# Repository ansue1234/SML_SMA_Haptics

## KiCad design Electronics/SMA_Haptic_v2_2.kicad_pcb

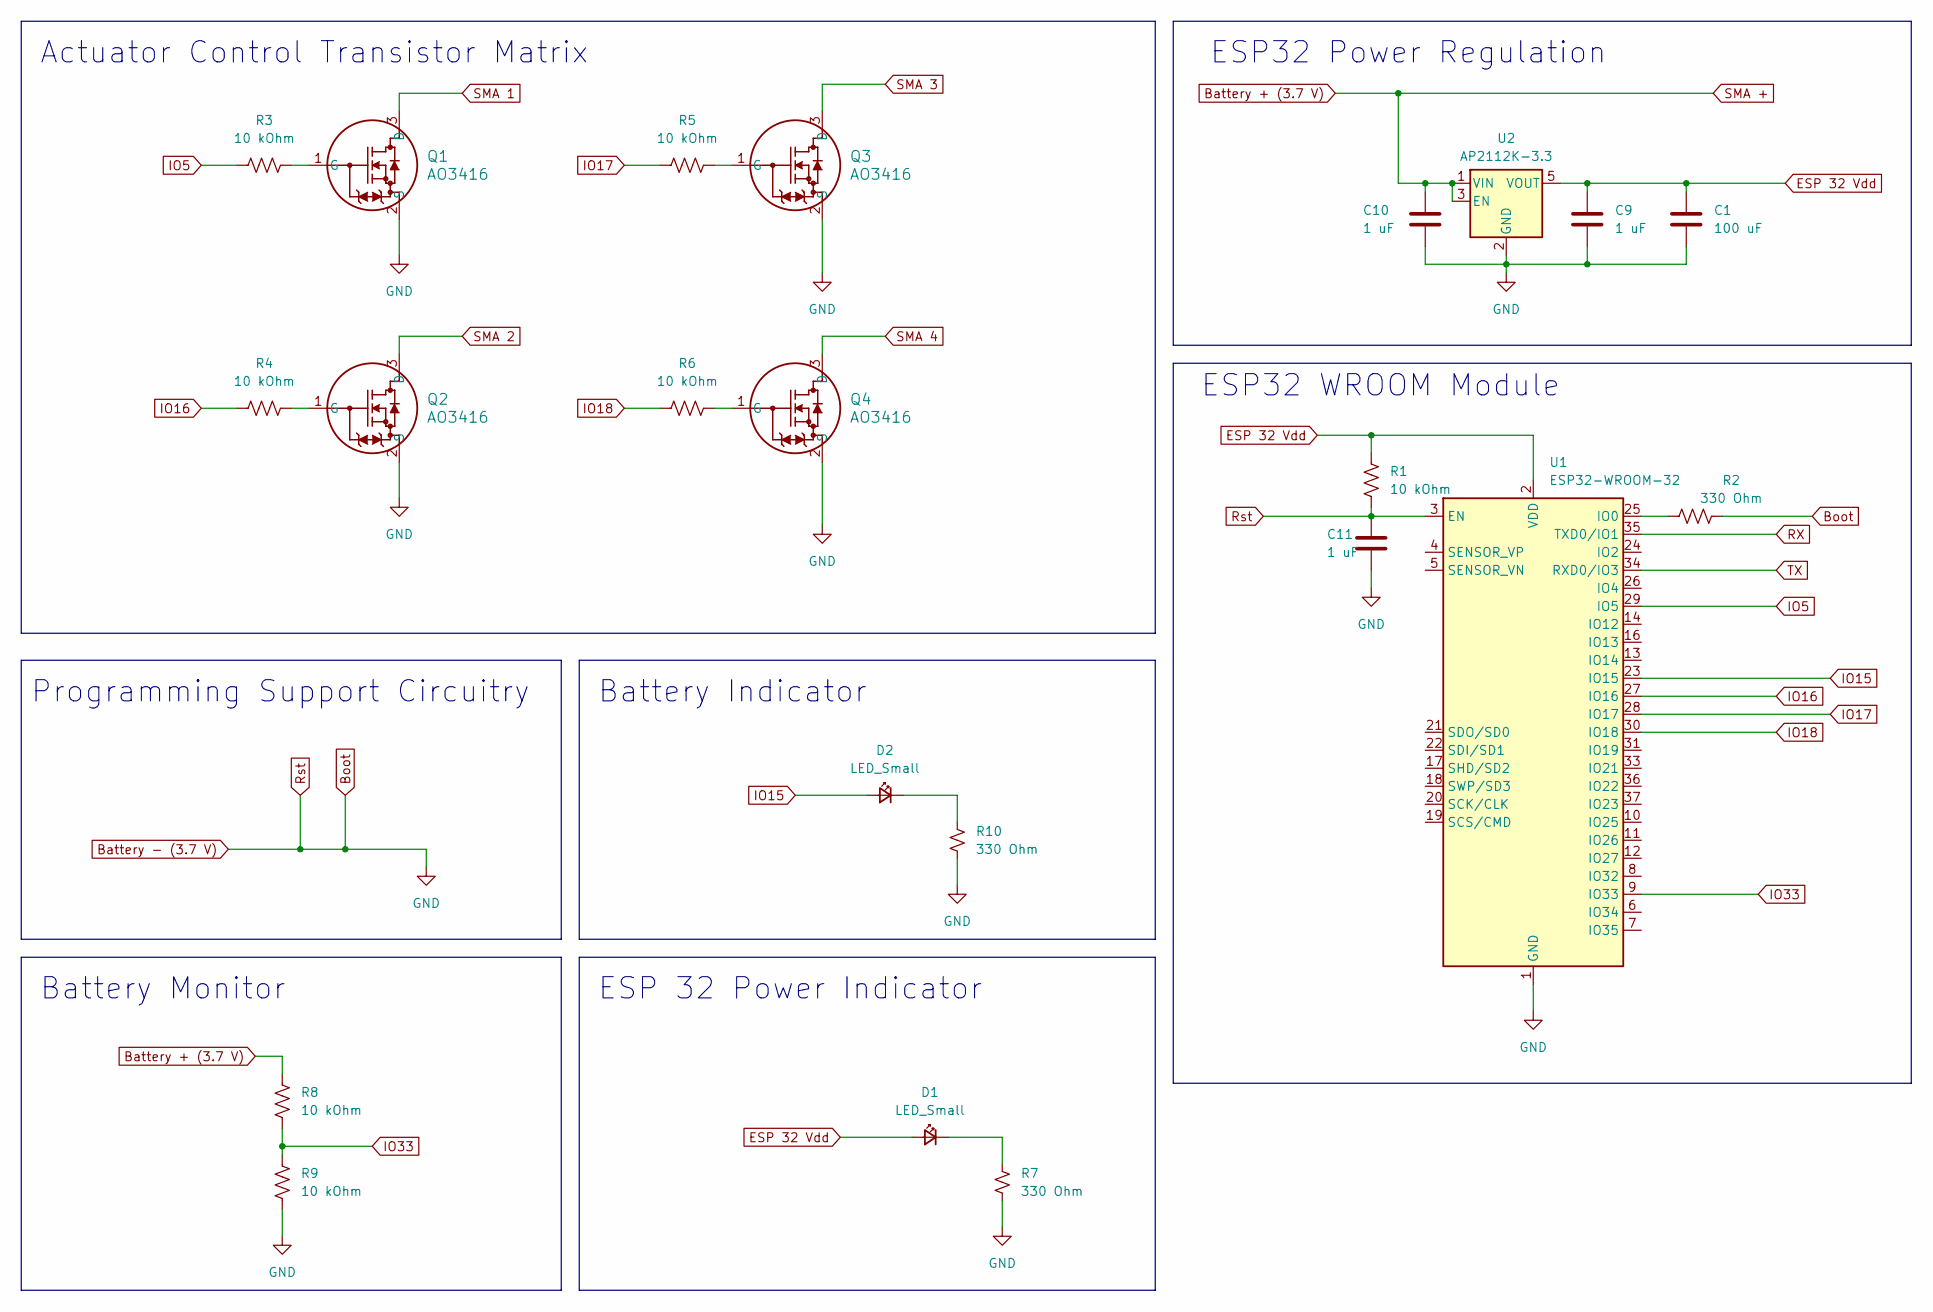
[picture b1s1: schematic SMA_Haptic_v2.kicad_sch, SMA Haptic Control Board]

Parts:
C1: 100 uF; C_1206_3216Metric_Pad1.33x1.80mm_HandSolder
C9, C10, C11: 1 uF; C_0603_1608Metric_Pad1.08x0.95mm_HandSolder
D1, D2: LED_Small; LED_0603_1608Metric_Pad1.05x0.95mm_HandSolder
Q1, Q2, Q3, Q4: AO3416; SOT23_AOS
R1, R3, R4, R5, R6, R8, R9: 10 kOhm; R_0805_2012Metric_Pad1.20x1.40mm_HandSolder
R2, R7, R10: 330 Ohm; R_0603_1608Metric_Pad0.98x0.95mm_HandSolder
U1: ESP32-WROOM-32
U2: AP2112K-3.3; SOT-23-5

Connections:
Battery + (3.7 V): C10.1, R8.2, U2.1 (VIN), U2.3 (EN)
Battery - (3.7 V): C1.2, C9.2, C10.2, C11.1, C11.2, Q1.2 (S), Q2.2 (S), Q3.2 (S), Q4.2 (S), R1.2, R2.2, R7.2, R9.1, R10.2, U1.1 (GND), U1.3 (EN), U1.15 (GND), U1.38 (GND), U1.39 (GND), U2.2 (GND)
ESP 32 Vdd: C1.1, C9.1, D1.2 (A), R1.1, U1.2 (VDD), U2.5 (VOUT)
IO5: R3.1, U1.29 (IO5)
IO15: D2.2 (A), U1.23 (IO15)
IO16: R4.1, U1.27 (IO16)
IO17: R5.1, U1.28 (IO17)
IO18: R6.1, U1.30 (IO18)
IO33: R8.1, R9.2, U1.9 (IO33)
unnamed: D1.1 (K), R7.1
unnamed: D2.1 (K), R10.1
unnamed: Q1.1 (G), R3.2
unnamed: Q2.1 (G), R4.2
unnamed: Q3.1 (G), R5.2
unnamed: Q4.1 (G), R6.2
unnamed: R2.1, U1.25 (IO0)
RX: U1.35 (TXD0/IO1)
SMA 1: Q1.3 (D)
SMA 2: Q2.3 (D)
SMA 3: Q3.3 (D)
SMA 4: Q4.3 (D)
TX: U1.34 (RXD0/IO3)

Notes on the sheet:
Actuator Control Transistor Matrix
ESP 32 Power Indicator
Battery Indicator
ESP32 WROOM Module
Battery Monitor
Programming Support Circuitry
ESP32 Power Regulation

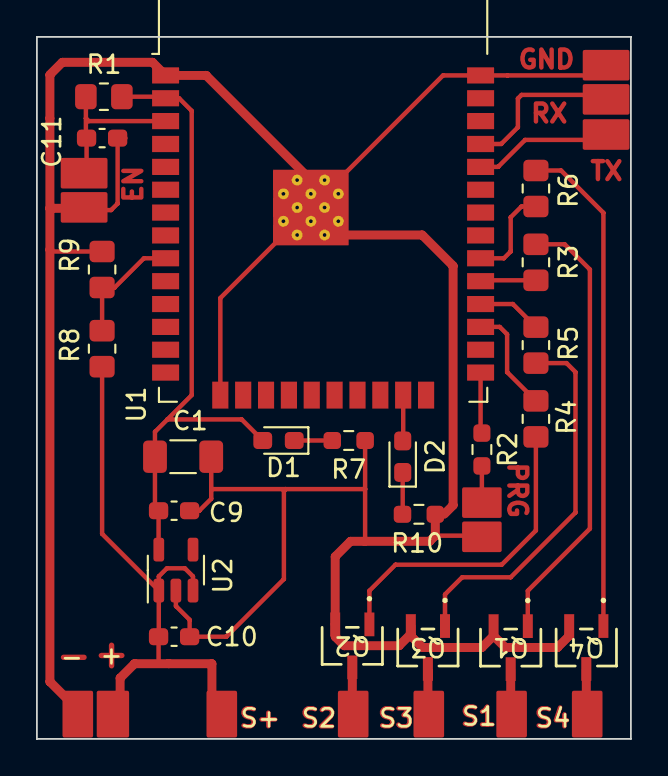
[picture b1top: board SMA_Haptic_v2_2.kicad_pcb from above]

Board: 2 copper layers, 33.0 x 39.0 mm, 22 parts (0 on the bottom side), 16 nets.

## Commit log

2025-04-22 public release
2025-04-22 VR demo code
